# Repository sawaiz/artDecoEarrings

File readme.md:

# Art Deco Earrings
Shimmering electronic earrings in the Art Deco style. Dangle style earring that just lightly shimmers when you are still, and glow brightly when dancing. The lights travel down the length of the earring revealing movement over time.

![shimmer]

The earrings use an IMU, sensing changes in acceleration and rotation and based on the magnitude of the change, the brightness is set. Each of the three axes of motion are mapped to a color so the color depends on the way you move.

## Design
The design follows the Art Deco style. Clean sharp lines, hard contrast, metallics including gold, and bold colors. A focus on materials and glamour. This can be seen in the sharp point on the bottom or the light ray motif running along the sides along with other small touches across the board.

![render-front]

### Electrical
The electrical design is made to be very minimal and manufacturable. Keeping all parts on one side and using no smaller the 0402 components helps with that. Total packages are also kept to a minimum to simplify assembly. The circuit has voltage range of 3.3V to 5.5V. It is expected to consume 5mA in low activity and about 25mA in high activity. A theoretical maximum consumption is 133.49mA. 

![schematic]

The [`schematic.pdf`](./docs/schematic.pdf) version is also available.

#### Microcontroller
Microchip's [ATtiny20](https://ww1.microchip.com/downloads/en/DeviceDoc/Atmel-2586-AVR-8-bit-Microcontroller-ATtiny25-ATtiny45-ATtiny85_Datasheet.pdf) in a QFN 4mmx4mm package was selected due to its size. Without getting into WLCSP, selecting a device with the correct peripherals that is smaller is difficult. It is a reasonably low cost 8-bit processor, able to be programmed through the Arduino IDE, somewhat low power, and could be prototyped with the PDIP package. It has limited RAM, but with only eight LEDs that is not a problem. 

The device is programed with a Tag-Connect [TC2030](https://www.tag-connect.com/product/tc2030-idc-nl) programing header that has the corresponding ICSP contacts on the back of the board along with the needed locating pins.

![render-back]

#### IMU
ST-Microelectronics's [LSM6DSM](https://www.st.com/resource/en/datasheet/lsm6dsm.pdf) available in a small (2.5mmx3mm) is a low power accelerometer and gyroscope with I2C and SPI. It is very low power and also has additional embedded functions that are not being used currently. 

#### LED Array
WorldSemi [WS2812B-2020](http://www.world-semi.com/DownLoadFile/140) RGB LEDs in the 2mmx2.2mm package provide the light. They come in a small package that can glow brightly and are addressable so only a single data line provides data to the whole array in a shift-register fashion.

![render-tip]

#### Power Supply
Microchip's [MIC5365](http://ww1.microchip.com/downloads/en/DeviceDoc/mic5365.pdf) and battery pads are the main power components. The 3.3V LDO linear regulator provides power to the microcontroller and IMU. There is no UVLO so it is recommended your battery has one. With voltage below 3.3V the output voltage corresponds to the input with the ~60mA drop, the board should continue working until 2.7V where the blue diode will cut out and the microcontroller falls out of it's speed grade and may not be able to maintain its clock speed. The two battery pads on the back are marked with plus and minus symbols and can have enameled wires soldered to them to provide power to the board.

![prototype-back]

#### Coating
After programming and testing, four thin coats of [OPI Top Coat](https://www.opi.com/shop-products/nail-care/top-base-coats/opi-top-coat) were added on top to secure the enameled wires and provide encapsulation. 

![prototype-encapsulated]

Then following the lines on the back silkscreen, the board is trimmed to its final dimensions removing the locating holes for the programmer.

![layout-trim]

## Firmware
The main loop is shown below (an excerpt from [main.cpp](./firmware/src/main.cpp)) and the logic is currently very minimal. The sensor is read every 25ms, and its current value is compared to the previous value. The magnitude of difference between those values is mapped (after dividing by 2^6 to reduce sensitivity) to the three colors, one for each axis.

All the LEDs are moved down one spot, and the calculated values are assigned to the top LED. As this repeats, the colors waterfall down the chain until they "fall off" at the end.

```cpp
void loop() {
  imu.readRawAccel();

  // Calculate change, and map to lower sensitivity
  uint8_t red =   abs((imu.accelData.x >> 6) - (prevX >> 6));
  uint8_t green = abs((imu.accelData.y >> 6) - (prevY >> 6));
  uint8_t blue =  abs((imu.accelData.z >> 6) - (prevZ >> 6));

  // Store current reading as new previous data
  prevX = imu.accelData.x;
  prevY = imu.accelData.y;
  prevZ = imu.accelData.z;

  // Shift all LEDs down one spot
  memmove(&leds[1], &leds[0], NUM_LEDS * sizeof(CRGB) - 1);
  // Set color of 0th LED
  leds[0] = CRGB(red, green, blue);
  FastLED.show();
  delay(25);
}
```

On boot there is a pulse of light from the acceleration vector of gravity being compared to the initial all zero values. 

### LSM6DM Driver
The driver is meant to be minimal and fast. Producing only `int16_t` values and no floating-point operations. It can access the accelerometer, gyroscope, and temperature sensor as well as set their max scale and rates.

### Compiling
It is set up to be compile through [PlatformIO](https://platformio.org/). More information can be found through its [doucmentation](https://docs.platformio.org/en/latest/). Changes may be need to the settings in the `ini` file.

### Flashing
An ICSP programmer along with the TagConnect programming header is needed to program the board. A [retaining clip](https://www.tag-connect.com/product/tc2030-clip-retaining-clip-board-for-tc2030-nl-cables) is useful for extended programing sessions.

Recommended programers are the [Atmel-ICE](https://www.microchip.com/DevelopmentTools/ProductDetails/ATATMEL-ICE) or [Adafruit's USBtinyISP](https://www.adafruit.com/product/46). Take care to remove the power target jumper if using the USBTinyISP as the IMU has an absolute max voltage of 4.8V. The board will need external power regardless for programming, so attach a battery.

Uploading using PlatformIO is currently used. Refer to [documentaiton](https://docs.platformio.org/en/latest/). Changes may be needed to the `ini` file settings.

### Fuses
The highest fuse bit in the low fuses needs to be to disable the `CKDIV8` flag. The fuses can either be flashed though PlatformIO as they are set in the `ini` file, or through avrdude as shown below.

```bash
avrdude -p t85 -c atmelice_isp -U lfuse:w:0xE2:m -U hfuse:w:0xdf:m -U efuse:w:0xff:m
```

### Timing Analysis
An extra GPIO was used toggling around the delay function. This will provide the approximate time the processor needs to be awake. There is a lot of overhead from the Arduino libraries. Running an empty loop takes ~700us (5600 cycles) from the end of the loop to the start of the next. 

![timingCapture]

The values were averaged over 64 samples and will not sum across the measurements due to noise but should be within 0.5%. The frequency value was taken to cross check the high and low time.

| Domain | Value | Unit | Percentage |
| -----  | -----:| ---- | ----------:|
| Full   | 26.33 | ms   |    100.00% |
| Sleep  | 24.67 | ms   |     93.70% |
| Active | 1.746 | ms   |      6.63% |

Based on that rough data, and the current draw values from the datasheet, we can estimate average power consumption.

```
4mA Active * 0.0663 = 0.2652 mA
1mA Idle   * 0.9370 = 0.9370 mA +
                      ------------
                      1.2022 mA
```

This can be significantly improved by switching to C to reduce the active time.

## BOM
The bill of materials is available in [`bom.csv`](bom.csv) and is copied into a table below.

| Ref Des                 | Qty | Manufacturer          | MPN               | Description                           |
| ----- | ---:| --------------------- | ----------------- | ------------------------------------- |
| C1    | 1   | Samsung               | CL05A105KQ5NNNC   | CAP: Ceramic 1uF 6.3V X5R 0402        |
| C2    | 1   | Taiyo Yuden           | JMK105BJ225KV-F   | CAP: Ceramic 2.2uF 6.3V X5R 0402      |
| C3    | 1   | Wuerth Elektronik     | 885012105010      | CAP: Ceramic 0.1uF 10V X5R 0402       |
| D1-D8 | 8   | WorldSemi             | WS2812B-2020      | LED: Addressable RGB (2x2)            |
| R1 R2 | 2   | Stackpole Electronics | RMCF0402JT10K0    | RES: 10K OHM 5% 1/16W 0402            |
| U1    | 1   | Microchip             | MIC5365-3.3YMT-TZ | REG Linear 3.3V 150mA 4TMLF (1x1)     |
| U2    | 1   | Microchip             | ATTINY85-20MU     | MCU: AVR 8b 8KB Flash 20QFN (4x4)     |
| U3    | 1   | STMicroelectronics    | LSM6DSMTR         | IMU: Accel/Gyro I2C/SPI 14LGA (2.5x3) |

A [Octopart](https://octopart.com/bom-tool/vS6z9Vt5) BOM is also available to simplify ordering. 

## Assembly
Assembly is all surface mount with components on one side of the board to make PNP assembly easy. The layout layer duplicated below lists components by their reference designators and values.

![layout-fab]

Solder paste can be applied with 25ga+ syringe, or with a stencil of the top paste layer. The components can then be placed, taking note of those that are polarity dependent, being U1-U3 and D1-D8 as marked in the assembly layer. A standard reflow profile, a hotplate, or a hot air rework station should work equally well. Inspect the side joints of the microcontroller as they will experience a lot of stress when trimming the board.

![layout-trim]

Two pads on the back are to provide power from enameled wire that can be soldered, and then twisted and routed out through the mounting hole on top. Then after final testing the device can be encapsulated and then trimmed.

![prototype-macro]
A detail image of a fully assembled prototype before trimming

## PCB Ordering
The board is a two-layer polyimide flex with 6/6mil spacing, plated through vias. These are generally the defaults boards so they can be made by most fabrication houses provided flex is an available option. A set of three was purchased at [Oshpark](http://oshpark.com/) for 2.00 USD and a shared project is available [here](https://oshpark.com/shared_projects/V0E4EFRY).

![prototype-boards]

A full set of gerbers are also available in [`./docs/gerbers`](./docs/gerbers). They have been visually checked although the fabrication of the prototypes was from the KiCad source file.

### Dimensions
The board is rather small so it may need to be panelized for some manufacturers. 

*PCB Dimensions*
|        | Width | Height |
| ------ | ----- | ------ |
| Inches | 1.53  |  0.26  |
| mm     | 38.9  |   6.6  |

Since its tapered, it can be placed in an alternating orientation for better space utilization.

![layout-dim]

Dimensions of board after being trimmed to size.

## To-Do
- [ ] Change delay to sleep
- [ ] Move code to simple makefile
- [ ] Find ideal low power IMU rate
- [ ] Switch to C for performance improvements
- [ ] Add passives (R & C) to project library

<!-- Images -->
[shimmer]:                /docs/shimmer.gif                "Animated view of the shimmer"
[render-front]:           /docs/render-front.jpg           "Ray Traced render of front"
[render-back]:            /docs/render-back.jpg            "Ray Traced render of back"
[render-tip]:             /docs/render-tip.png             "Render of tip"
[render-rays]:            /docs/render-rays.png            "Render of ray motif"
[prototype-boards]:       /docs/prototype-boards.jpg       "Three fabricated unpopulated boards"
[prototype-scale]:        /docs/prototype-scale.jpg        "Assembled prototype with various coins as scale"
[prototype-encapsulated]: /docs/prototype-encapsulated.jpg "Nail polish topcoat encapsulation detail"
[prototype-back]:         /docs/prototype-back.jpg         "Back of assembled prototype boards"
[prototype-macro]:        /docs/prototype-macro.jpg        "Detail of fully assembled board"
[layout-dim]:             /docs/layout-dim.png             "Final dimensions after trimming"
[layout-fab]:             /docs/layout-fab.png             "Component placement for fabrication"
[layout-trim]:            /docs/layout-trim.png            "Trimming line on back of boards"
[schematic]:              /docs/schematic.png              "Full schematic"
[timingcapture]:          /docs/timingCapture.png          "Timing of"

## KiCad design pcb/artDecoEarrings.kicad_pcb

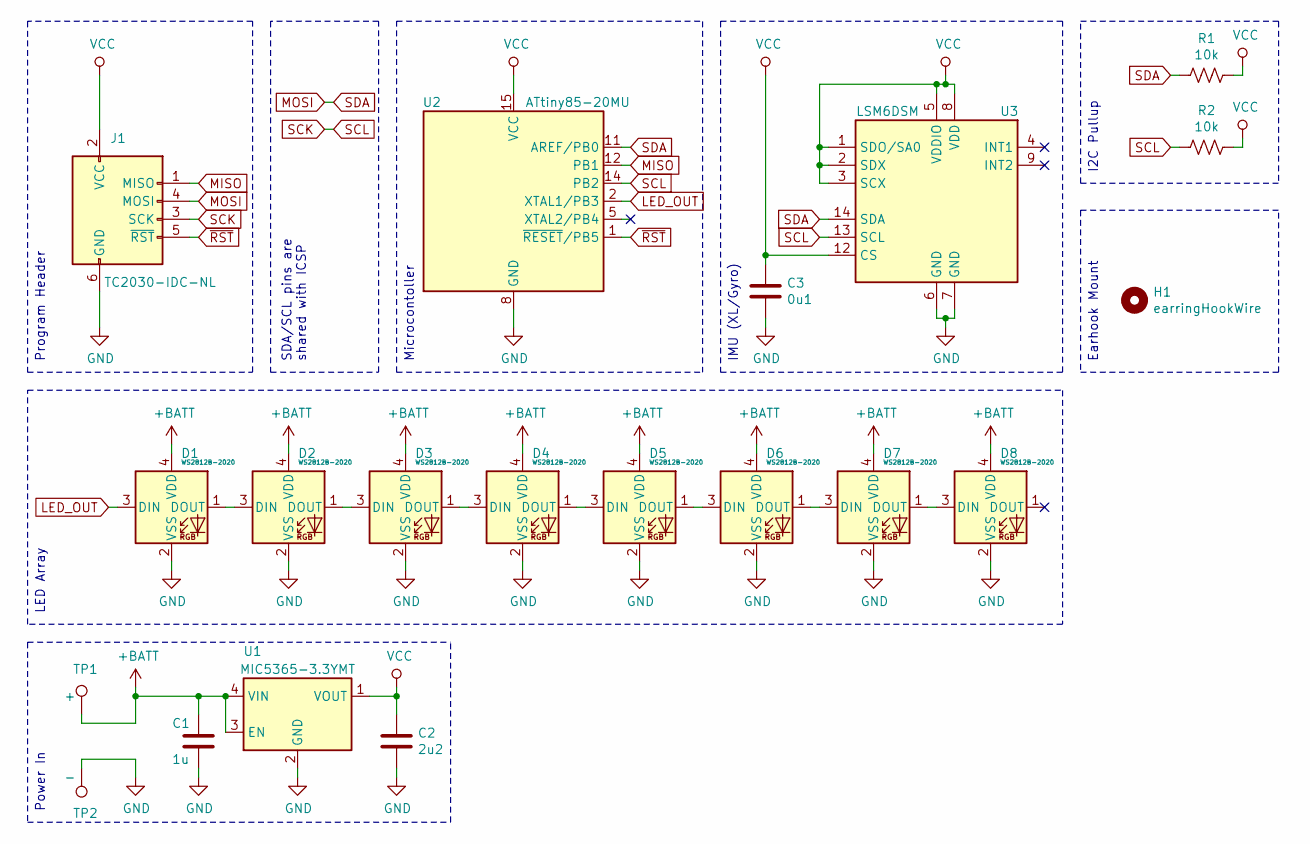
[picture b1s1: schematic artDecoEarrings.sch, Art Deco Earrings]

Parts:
C1: 1u; C_0402_1005Metric
C2: 2u2; C_0402_1005Metric
C3: 0u1; C_0402_1005Metric
D1, D2, D3, D4, D5, D6, D7, D8: WS2812B-2020
H1: earringHookWire
J1: TC2030-IDC-NL; Tag-Connect_TC2030-IDC-NL_2x03_P1.27mm_Vertical
R1, R2: 10k; R_0402_1005Metric
TP1: +; TestPoint_Pad_D1.5mm
TP2: -; TestPoint_Pad_D1.5mm
U1: MIC5365-3.3YMT; MIC5365
U2: ATtiny85-20MU; QFN-20-1EP_4x4mm_P0.5mm_EP2.6x2.6mm
U3: LSM6DSM; LGA-14_3x2.5mm_6-6

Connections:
+BATT: C1.1, D1.4 (VDD), D2.4 (VDD), D3.4 (VDD), D4.4 (VDD), D5.4 (VDD), D6.4 (VDD), D7.4 (VDD), D8.4 (VDD), TP1.1, U1.3 (EN), U1.4 (VIN); also elsewhere on the board
GND: C1.2, C2.2, C3.2, D1.2 (VSS), D2.2 (VSS), D3.2 (VSS), D4.2 (VSS), D5.2 (VSS), D6.2 (VSS), D7.2 (VSS), D8.2 (VSS), J1.6 (GND), TP2.1, U1.2 (GND), U2.8 (GND), U2.21 (GND), U3.6 (GND), U3.7 (GND); also elsewhere on the board
LED_OUT: D1.3 (DIN), U2.2 (XTAL1/PB3)
MISO: J1.1 (MISO), U2.12 (PB1)
MOSI: J1.4 (MOSI), R1.2, U2.11 (AREF/PB0), U3.14 (SDA)
unnamed: D1.1 (DOUT), D2.3 (DIN)
unnamed: D2.1 (DOUT), D3.3 (DIN)
unnamed: D3.1 (DOUT), D4.3 (DIN)
unnamed: D4.1 (DOUT), D5.3 (DIN)
unnamed: D5.1 (DOUT), D6.3 (DIN)
unnamed: D6.1 (DOUT), D7.3 (DIN)
unnamed: D7.1 (DOUT), D8.3 (DIN)
SCK: J1.3 (SCK), R2.2, U2.14 (PB2), U3.13 (SCL)
VCC: C2.1, C3.1, J1.2 (VCC), R1.1, R2.1, U1.1 (VOUT), U2.15 (VCC), U3.1 (SDO/SA0), U3.2 (SDX), U3.3 (SCX), U3.5 (VDDIO), U3.8 (VDD), U3.12 (CS)
~RST: J1.5 (~RST), U2.1 (~RESET~/PB5)

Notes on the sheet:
Power In
I2C Pullup
Earhook Mount
SDA/SCL pins are shared with ICSP
LED Array
Program Header
Microcontoller
IMU (XL/Gyro)

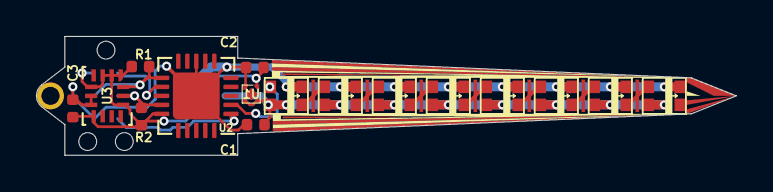
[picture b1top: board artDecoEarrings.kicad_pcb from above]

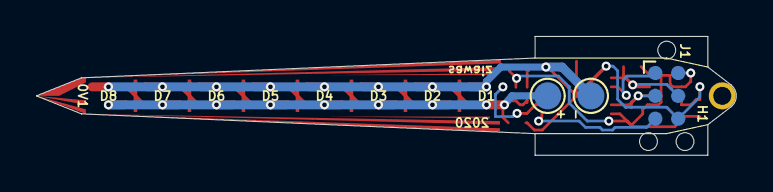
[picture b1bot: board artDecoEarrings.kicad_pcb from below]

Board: 2 copper layers, 38.9 x 6.6 mm, 20 parts (3 on the bottom side), 15 nets.

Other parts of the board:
+: +; TestPoint_Pad_D1.5mm
-: -; TestPoint_Pad_D1.5mm

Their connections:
+BATT: +.1; also elsewhere on the board
GND: -.1; also elsewhere on the board

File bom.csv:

Ref Des,Qty,Manufacturer,MPN,Description
C1,1,Samsung,CL05A105KQ5NNNC,CAP: Ceramic 1uF 6.3V X5R 0402
C2,1,Taiyo Yuden,JMK105BJ225KV-F,CAP: Ceramic 2.2uF 6.3V X5R 0402
C3,1,Wuerth Elektronik,885012105010,CAP: Ceramic 0.1uF 10V X5R 0402
D1 D2 D3 D4 D5 D6 D7 D8,8,WorldSemi,WS2812B-2020,LED: Addressable RGB (2x2)
R1 R2,2,Stackpole Electronics,RMCF0402JT10K0,RES: 10K OHM 5% 1/16W 0402
U1,1,Microchip,MIC5365-3.3YMT-TZ,REG Linear 3.3V 150mA 4TMLF (1x1)
U2,1,Microchip,ATTINY85-20MU,MCU: AVR 8b 8KB Flash 20QFN (4x4)
U3,1,STMicroelectronics,LSM6DSMTR,IMU: Accel/Gyro I2C/SPI 14LGA (2.5x3)

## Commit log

2020-05-01 Incresed gif size to full width of readme
2020-05-01 Added assembled macro shot
